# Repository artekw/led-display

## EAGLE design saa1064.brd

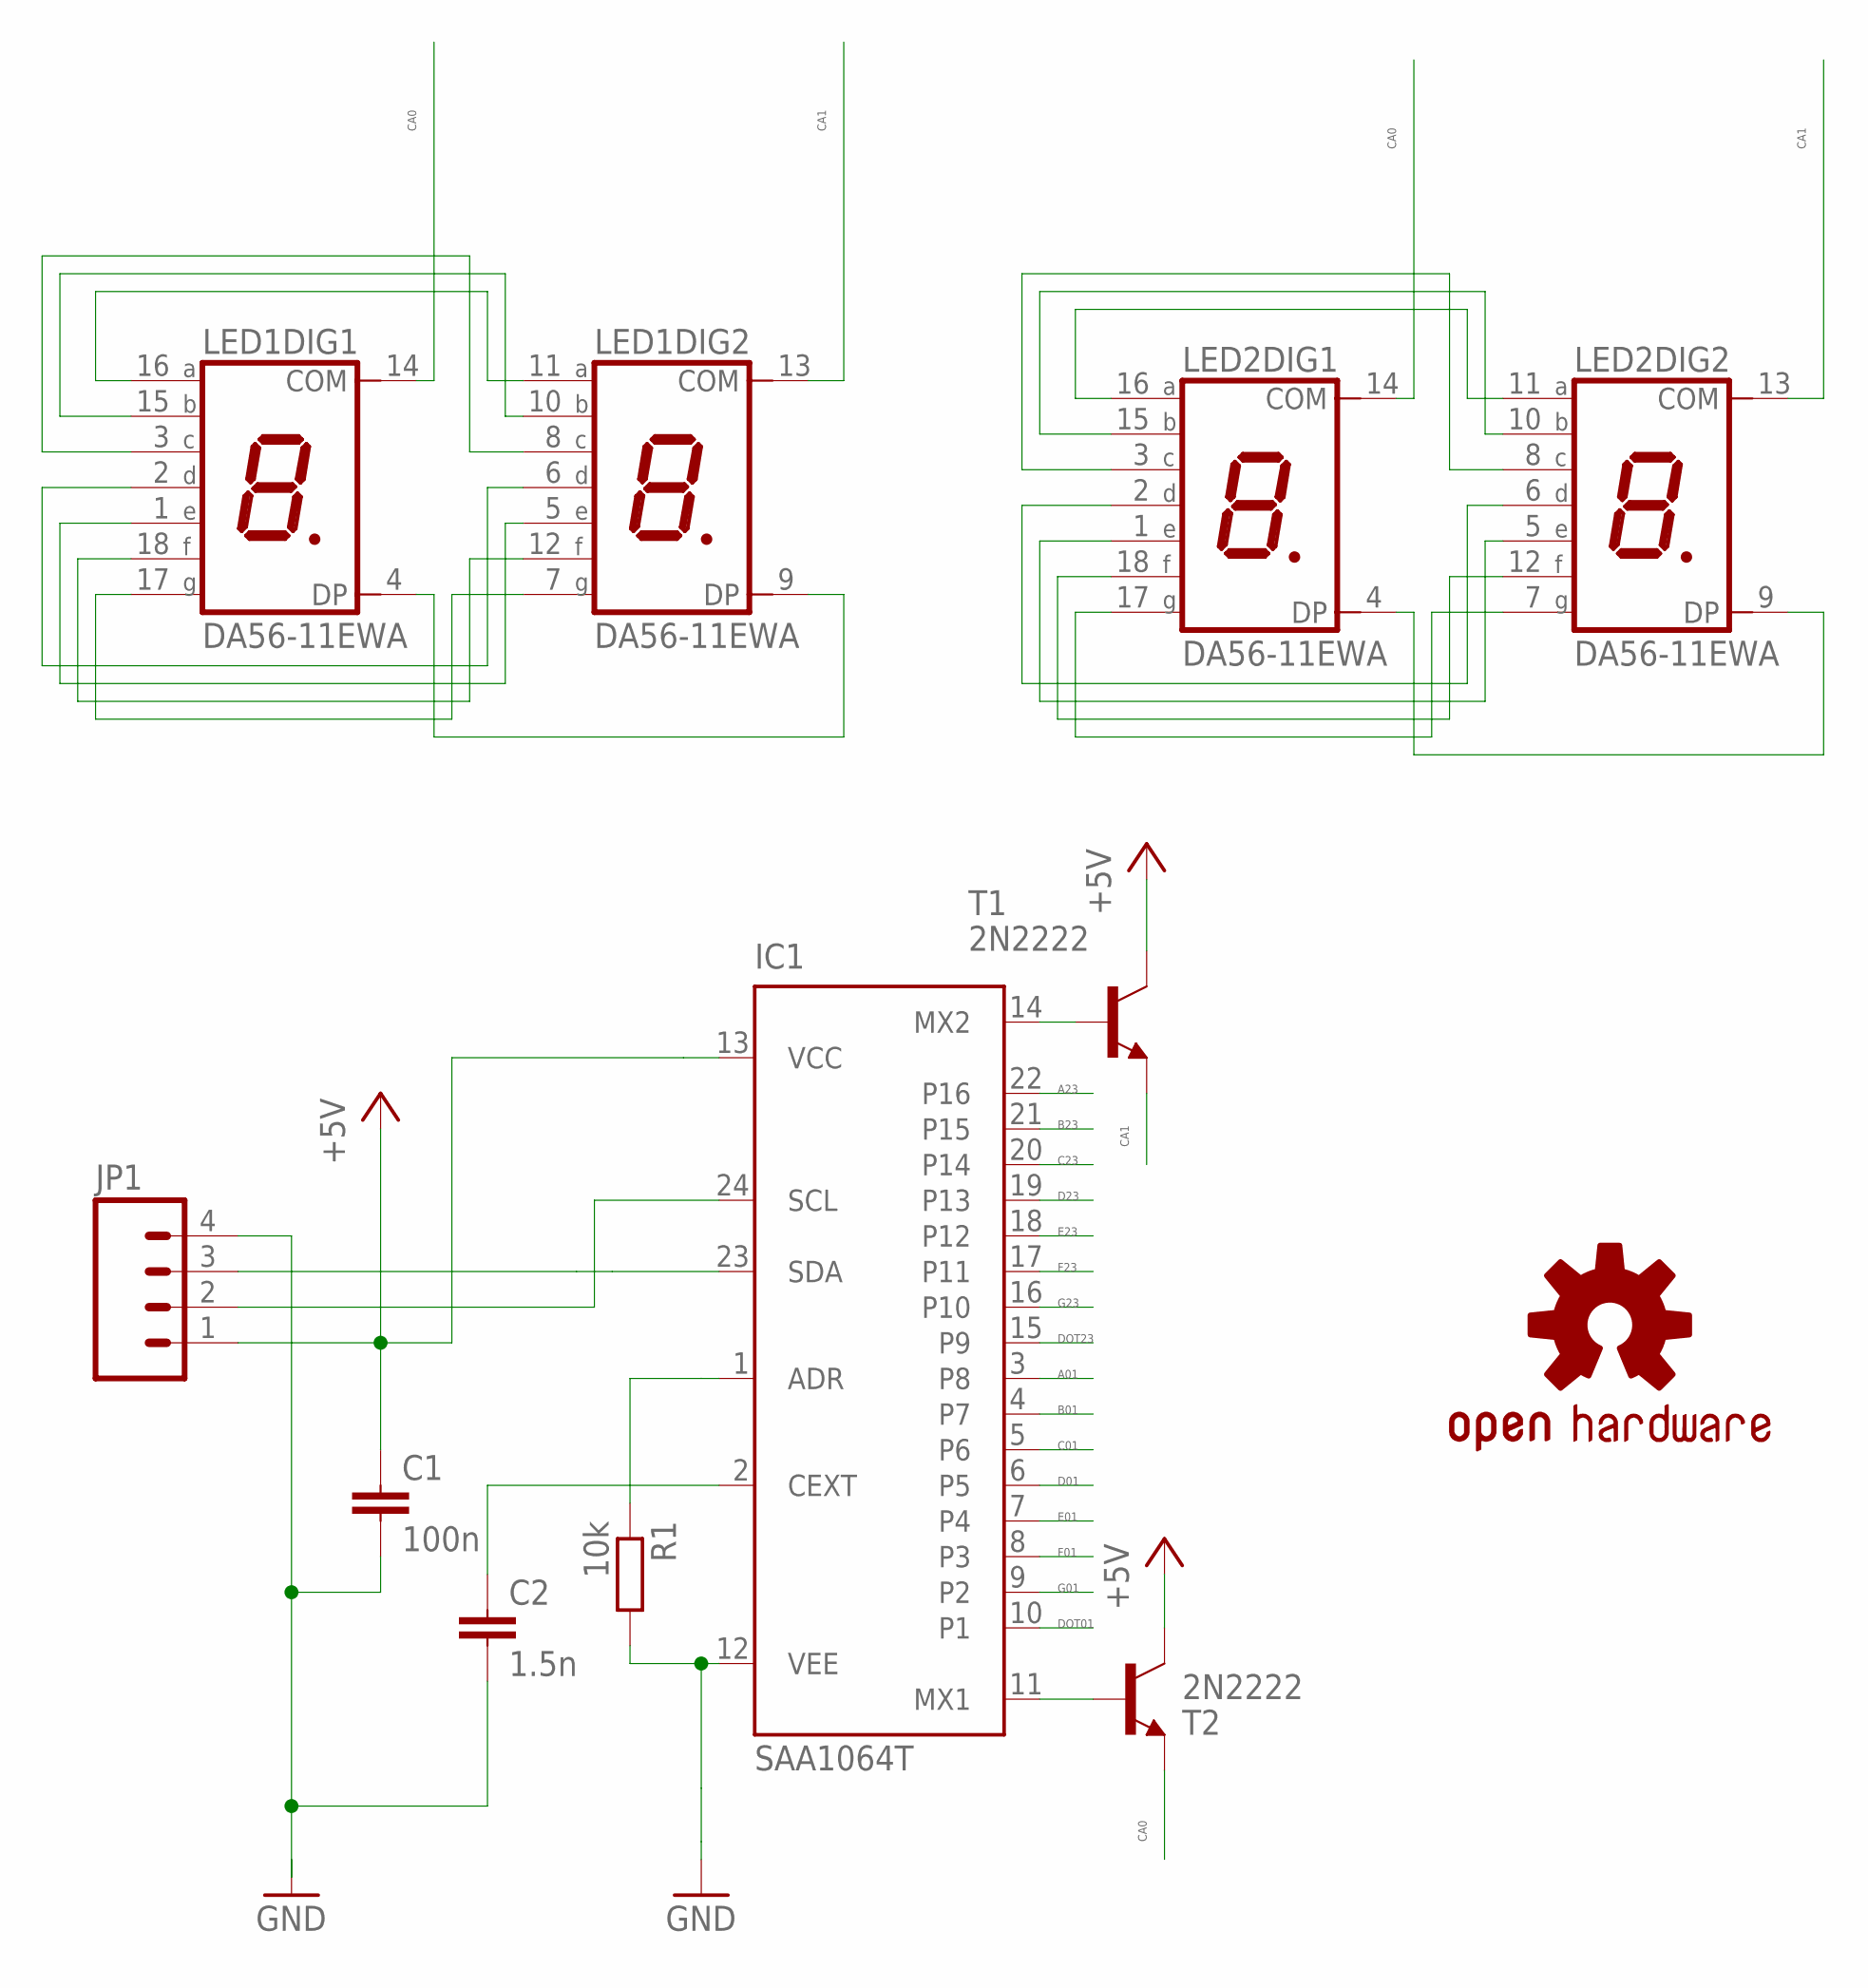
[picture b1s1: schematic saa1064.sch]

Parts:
C1: 100n; C0805K
C2: 1.5n; C0805K
IC1: SAA1064T; SO24
JP1: M04LONGPADS; 1X04_LONGPADS
LED1, LED2: DA56-11EWA; DA56
R1: 10k; M0805
T1, T2: 2N2222; TO92-EBC-OVAL
U$1: OSHW-LOGOS; OSHW-LOGO-S

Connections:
+5V: C1.1, IC1.13 (VCC), JP1.1, T1.C, T2.C
A01: IC1.3 (P8), LED1.11 (A), LED1.16 (A)
A23: IC1.22 (P16), LED2.11 (A), LED2.16 (A)
B01: IC1.4 (P7), LED1.10 (B), LED1.15 (B)
B23: IC1.21 (P15), LED2.10 (B), LED2.15 (B)
C01: IC1.5 (P6), LED1.3 (C), LED1.8 (C)
C23: IC1.20 (P14), LED2.3 (C), LED2.8 (C)
CA0: LED1.14 (COM), LED2.14 (COM), T2.E
CA1: LED1.13 (COM), LED2.13 (COM), T1.E
D01: IC1.6 (P5), LED1.2 (D), LED1.6 (D)
D23: IC1.19 (P13), LED2.2 (D), LED2.6 (D)
DOT01: IC1.10 (P1), LED1.4 (DP), LED1.9 (DP)
DOT23: IC1.15 (P9), LED2.4 (DP), LED2.9 (DP)
E01: IC1.7 (P4), LED1.1 (E), LED1.5 (E)
E23: IC1.18 (P12), LED2.1 (E), LED2.5 (E)
F01: IC1.8 (P3), LED1.12 (F), LED1.18 (F)
F23: IC1.17 (P11), LED2.12 (F), LED2.18 (F)
G01: IC1.9 (P2), LED1.7 (G), LED1.17 (G)
G23: IC1.16 (P10), LED2.7 (G), LED2.17 (G)
GND: C1.2, C2.2, IC1.12 (VEE), JP1.4, R1.2
unnamed: IC1.1 (ADR), R1.1
unnamed: C2.1, IC1.2 (CEXT)
unnamed: IC1.11 (MX1), T2.B
unnamed: IC1.14 (MX2), T1.B
SCL: IC1.24 (SCL), JP1.2
SDA: IC1.23 (SDA), JP1.3

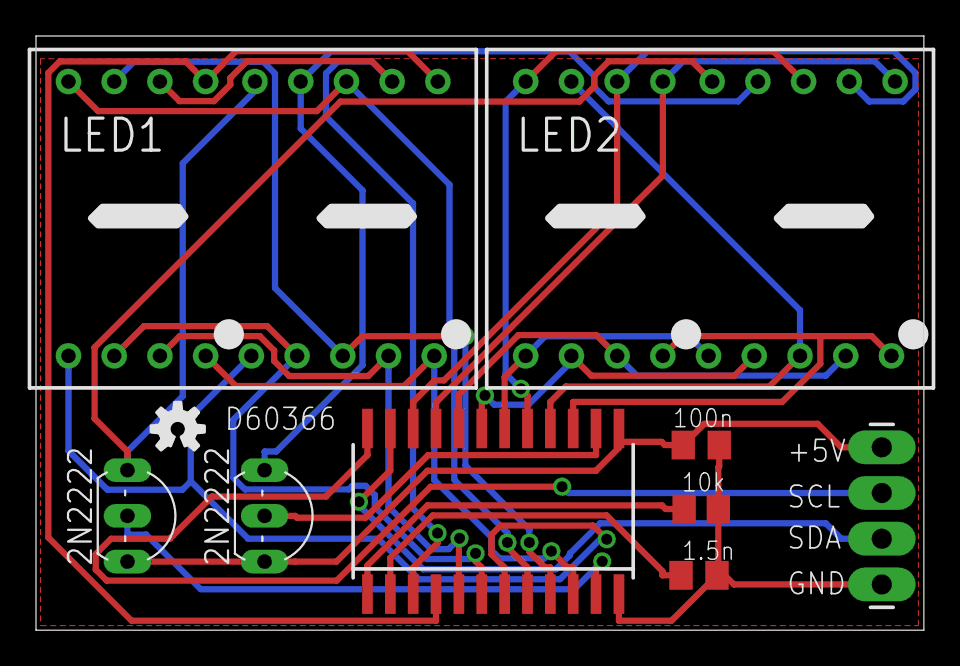
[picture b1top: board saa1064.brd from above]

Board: 2 copper layers, 49.3 x 33.0 mm, 10 parts (0 on the bottom side), 26 nets.
